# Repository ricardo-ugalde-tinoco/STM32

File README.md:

# STM32
The design of this board allowed me to familiarise myself with the KiCAD 7.0 interface. I used an STM32F103C8T6 microcontroller with a 16 MHz AN2867 oscillator crystal, programmable via USB Micro type B.

Screenshot of the completed model.

As I went deeper into PCB design, I noticed some errors that affect the aesthetics, but not the performance, so I decided to correct them.
Among the list of improvements is:
- Eliminate tight angles on the tracks.
- Put the 3D model of the Micro USB port.
- Reducing the number of vias on the board.
- Redesigning the shape of the PCB board.

Screenshot of the final model.

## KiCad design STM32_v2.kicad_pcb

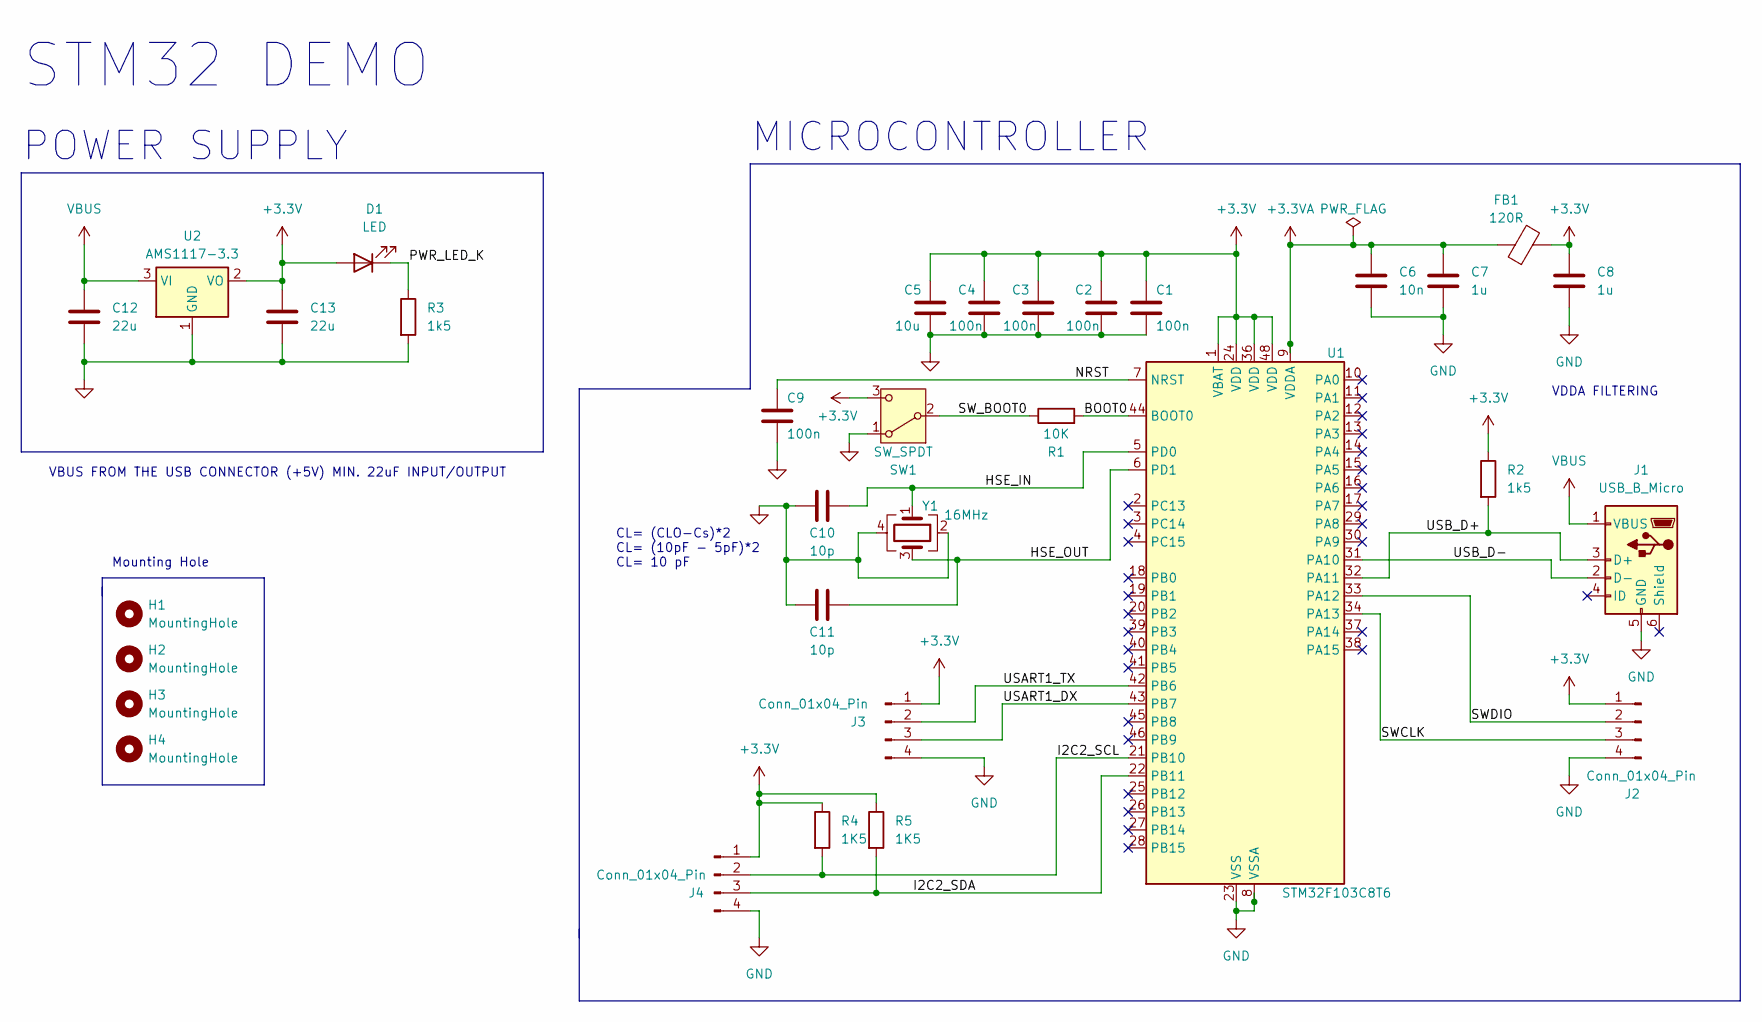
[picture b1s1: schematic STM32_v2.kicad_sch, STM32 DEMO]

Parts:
C1, C2, C3, C4, C9: 100n; C_0402_1005Metric
C5: 10u; C_0603_1608Metric
C6: 10n; C_0402_1005Metric
C7, C8: 1u; C_0402_1005Metric
C10, C11: 10p; C_0402_1005Metric
C12, C13: 22u; C_0805_2012Metric
D1: LED; LED_0603_1608Metric
FB1: 120R; L_0603_1608Metric
H1, H2, H3, H4: MountingHole; MountingHole_2.2mm_M2
J1: USB_B_Micro; USB_Micro-B_Wuerth_629105150521
J2, J3, J4: Conn_01x04_Pin; PinHeader_1x04_P2.54mm_Vertical
R1: 10K; R_0402_1005Metric
R2, R3: 1k5; R_0402_1005Metric
R4, R5: 1K5; R_0402_1005Metric
SW1: SW_SPDT; SW_SPDT_PCM12
U1: STM32F103C8T6; LQFP-48_7x7mm_P0.5mm
U2: AMS1117-3.3; SOT-223-3_TabPin2
Y1: 16MHz; Crystal_SMD_3225-4Pin_3.2x2.5mm

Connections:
+3.3V: C1.1, C2.1, C3.1, C4.1, C5.1, C8.1, C13.1, D1.2 (A), FB1.2, J2.1, J3.1, J4.1, R2.1, R4.1, R5.1, SW1.3 (C), U1.1 (VBAT), U1.24 (VDD), U1.36 (VDD), U1.48 (VDD), U2.2 (VO)
+3.3VA: C6.1, C7.1, FB1.1, U1.9 (VDDA)
/BOOT0: R1.2, U1.44 (BOOT0)
/HSE_IN: C10.2, U1.5 (PD0), Y1.1
/HSE_OUT: C11.2, U1.6 (PD1), Y1.3
/I2C2_SCL: J4.2, R4.2, U1.21 (PB10)
/I2C2_SDA: J4.3, R5.2, U1.22 (PB11)
/NRST: C9.1, U1.7 (NRST)
/PWR_LED_K: D1.1 (K), R3.1
/SWCLK: J2.3, U1.34 (PA13)
/SWDIO: J2.2, U1.33 (PA12)
/SW_BOOT0: R1.1, SW1.2 (B)
/USART1_DX: J3.3, U1.43 (PB7)
/USART1_TX: J3.2, U1.42 (PB6)
/USB_D+: J1.3 (D+), R2.2, U1.32 (PA11)
/USB_D-: J1.2 (D-), U1.31 (PA10)
GND: C1.2, C2.2, C3.2, C4.2, C5.2, C6.2, C7.2, C8.2, C9.2, C10.1, C11.1, C12.2, C13.2, J1.5 (GND), J2.4, J3.4, J4.4, R3.2, SW1.1 (A), U1.8 (VSSA), U1.23 (VSS), U1.35 (VSS), U1.47 (VSS), U2.1 (GND), Y1.2, Y1.4
VBUS: C12.1, J1.1 (VBUS), U2.3 (VI)

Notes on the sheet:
VDDA FILTERING
POWER SUPPLY
Mounting Hole
CL= (CLO-Cs)*2 CL= (10pF - 5pF)*2 CL= 10 pF
MICROCONTROLLER
VBUS FROM THE USB CONNECTOR (+5V) MIN. 22uF INPUT/OUTPUT
STM32 DEMO

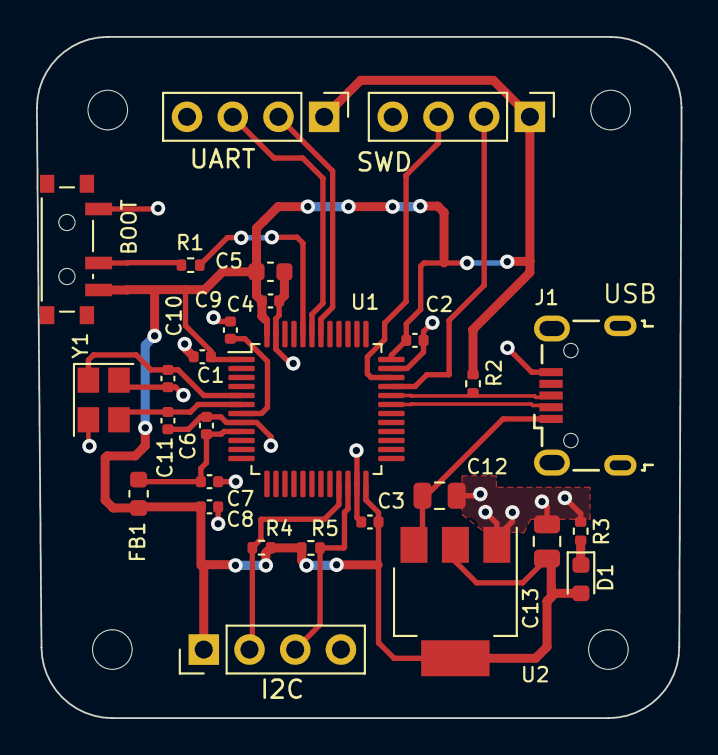
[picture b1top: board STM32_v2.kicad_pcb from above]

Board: 2 copper layers, 35.8 x 37.8 mm, 32 parts (0 on the bottom side), 18 nets.
